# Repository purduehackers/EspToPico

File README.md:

# EspToPico
This is a converter board for an ESP32 to a Pi Pico for the purposes of the Sign Project.

The next revision of the board (3) should fix the following problems:
- It is impossible to program the board without resorting to using the bodged boot button. The official ESP32 dev board uses the serial chip to reset the ESP32 and put it in boot mode. Schematics are available online. This would be ideal.
- The button switch and LED lines had to be reversed here since the LED line was sent to an input-only pin. I reversed the labels for rev 2, but now there is a mismatch to the motherboard. This could be fixed later but it doesn't matter very much.
- The EEPROM MOSI, SCK, and CS lines are assigned to an input-only pin, rendering the EEPROM inaccessible. The ESP32 has enough storage to make this a non-issue, but it is still a problem. The easiest fix would be to switch the EEPROM MISO and MOSI lines then move the SCK and CS lines to regular GPIOs like GPIO 2 and 13.

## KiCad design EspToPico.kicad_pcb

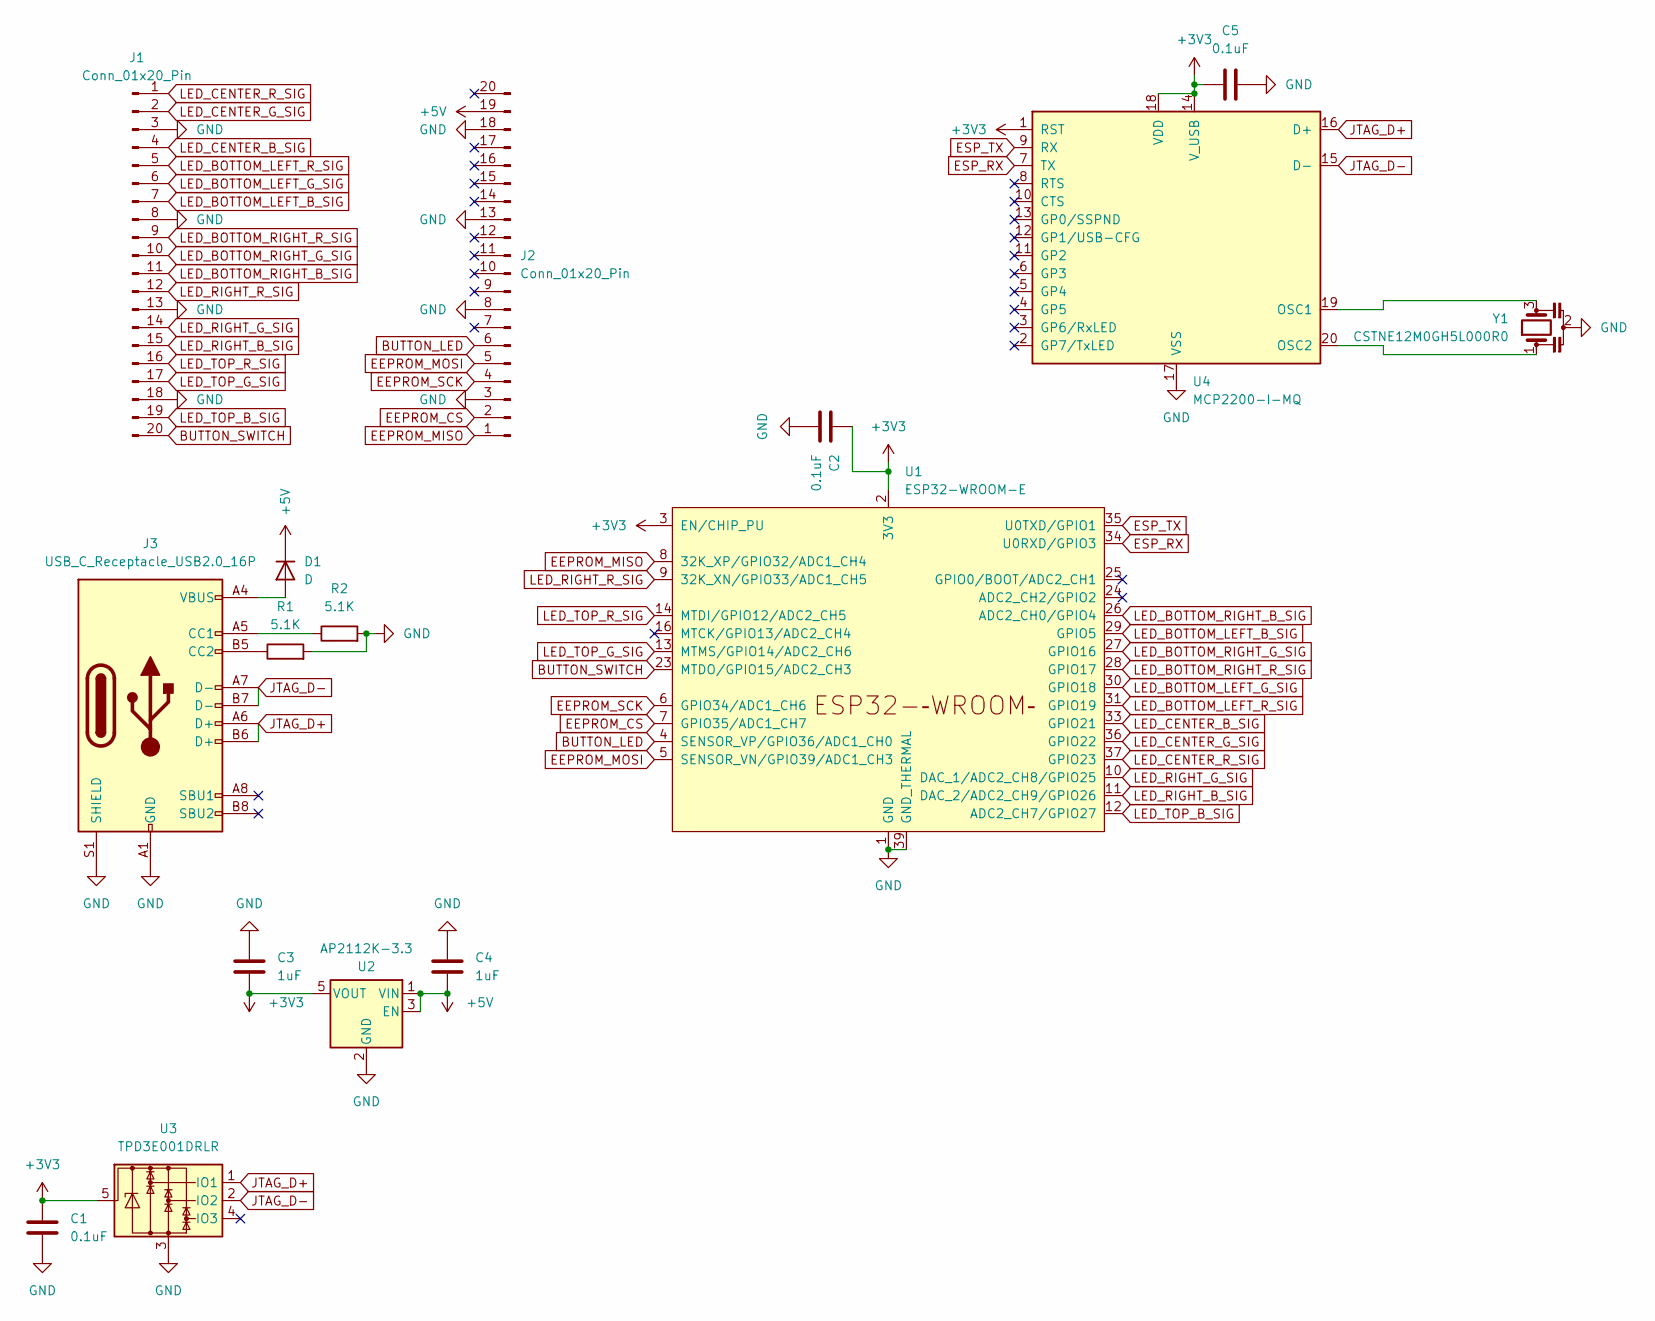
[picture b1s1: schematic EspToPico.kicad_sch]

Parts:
C1, C2: 0.1uF; C_0402_1005Metric
C3, C4: 1uF; C_0402_1005Metric
C5: 0.1uF
D1: D; D_SOD-323; LCSC C78740
J1, J2: Conn_01x20_Pin; PinHeader_1x20_P2.54mm_Vertical
J3: USB_C_Receptacle_USB2.0_16P; USB_C_Receptacle_GCT_USB4105-xx-A_16P_TopMnt_Horizontal; LCSC C2835315
R1, R2: 5.1K; R_0402_1005Metric
U1: ESP32-WROOM-E; ESP32-WROOM-32E
U2: AP2112K-3.3; SOT-23-5
U3: TPD3E001DRLR; SOT-553; LCSC C470828
U4: MCP2200-I-MQ; QFN-20-1EP_5x5mm_P0.65mm_EP3.35x3.35mm
Y1: CSTNE12M0GH5L000R0; CSTCE12M0G15L

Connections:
+3V3: C1.1, C2.1, C3.2, C5.1, U1.2 (3V3), U1.3 (EN/CHIP_PU), U2.5 (VOUT), U3.5, U4.1 (RST), U4.14 (V_USB), U4.18 (VDD)
+5V: C4.2, D1.1 (K), J2.19, U2.1 (VIN), U2.3 (EN)
BUTTON_LED: J2.6, U1.4 (SENSOR_VP/GPIO36/ADC1_CH0)
BUTTON_SWITCH: J1.20, U1.23 (MTDO/GPIO15/ADC2_CH3)
EEPROM_CS: J2.2, U1.7 (GPIO35/ADC1_CH7)
EEPROM_MISO: J2.1, U1.8 (32K_XP/GPIO32/ADC1_CH4)
EEPROM_MOSI: J2.5, U1.5 (SENSOR_VN/GPIO39/ADC1_CH3)
EEPROM_SCK: J2.4, U1.6 (GPIO34/ADC1_CH6)
ESP_RX: U1.34 (U0RXD/GPIO3), U4.7 (TX)
ESP_TX: U1.35 (U0TXD/GPIO1), U4.9 (RX)
GND: C1.2, C2.2, C3.1, C4.1, C5.2, J1.3, J1.8, J1.13, J1.18, J2.3, J2.8, J2.13, J2.18, J3.A1 (GND), J3.A12 (GND), J3.B1 (GND), J3.B12 (GND), J3.S1 (SHIELD), R1.2, R2.2, U1.1 (GND), U1.15 (GND), U1.38 (GND), U1.39 (GND_THERMAL), U2.2 (GND), U3.3, U4.17 (VSS), Y1.2
JTAG_D+: J3.A6 (D+), J3.B6 (D+), U3.1 (IO1), U4.16 (D+)
JTAG_D-: J3.A7 (D-), J3.B7 (D-), U3.2 (IO2), U4.15 (D-)
LED_BOTTOM_LEFT_B_SIG: J1.7, U1.29 (GPIO5)
LED_BOTTOM_LEFT_G_SIG: J1.6, U1.30 (GPIO18)
LED_BOTTOM_LEFT_R_SIG: J1.5, U1.31 (GPIO19)
LED_BOTTOM_RIGHT_B_SIG: J1.11, U1.26 (ADC2_CH0/GPIO4)
LED_BOTTOM_RIGHT_G_SIG: J1.10, U1.27 (GPIO16)
LED_BOTTOM_RIGHT_R_SIG: J1.9, U1.28 (GPIO17)
LED_CENTER_B_SIG: J1.4, U1.33 (GPIO21)
LED_CENTER_G_SIG: J1.2, U1.36 (GPIO22)
LED_CENTER_R_SIG: J1.1, U1.37 (GPIO23)
LED_RIGHT_B_SIG: J1.15, U1.11 (DAC_2/ADC2_CH9/GPIO26)
LED_RIGHT_G_SIG: J1.14, U1.10 (DAC_1/ADC2_CH8/GPIO25)
LED_RIGHT_R_SIG: J1.12, U1.9 (32K_XN/GPIO33/ADC1_CH5)
LED_TOP_B_SIG: J1.19, U1.12 (ADC2_CH7/GPIO27)
LED_TOP_G_SIG: J1.17, U1.13 (MTMS/GPIO14/ADC2_CH6)
LED_TOP_R_SIG: J1.16, U1.14 (MTDI/GPIO12/ADC2_CH5)
unnamed: D1.2 (A), J3.A4 (VBUS), J3.A9 (VBUS), J3.B4 (VBUS), J3.B9 (VBUS)
unnamed: J3.A5 (CC1), R2.1
unnamed: J3.B5 (CC2), R1.1
unnamed: U4.19 (OSC1), Y1.3
unnamed: U4.20 (OSC2), Y1.1

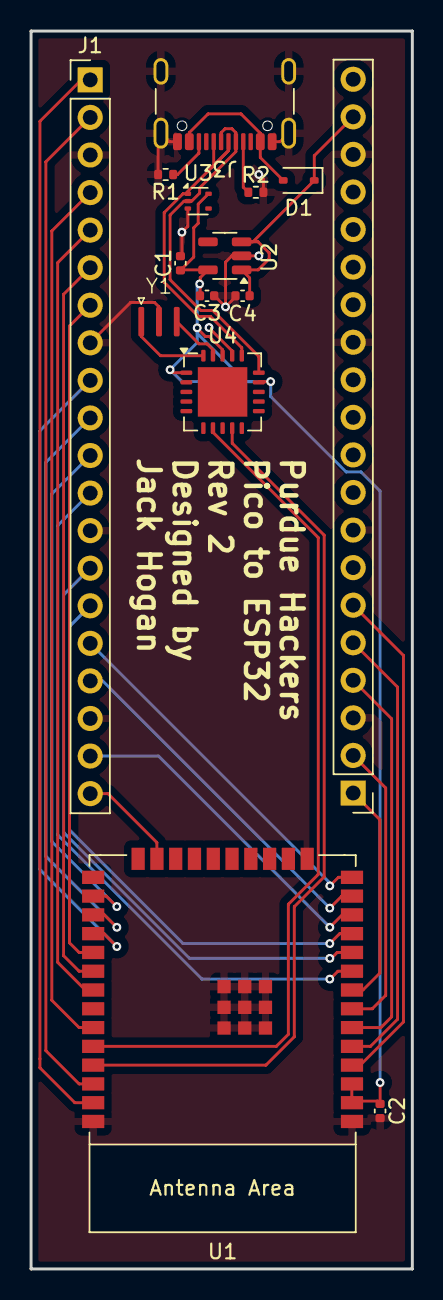
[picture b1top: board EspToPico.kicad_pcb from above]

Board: 2 copper layers, 25.8 x 83.7 mm, 15 parts (0 on the bottom side), 33 nets.

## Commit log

2024-08-24 Initial
2024-08-24 Removed sleep depravation
2024-08-25 Layout
2024-08-26 Added capacitors to the voltage regulator, added through-hole to the ESP32 for hand-soldering, and updated some routing.
2024-09-23 Started conversion to ESP32
2024-09-24 Updated to ESP32
2024-09-24 Fixed silkscreen
2024-09-24 Electrical and Routing fixes
2024-10-12 Reversed button switch and LED pins since the original LED pin is input only
2024-10-12 Added README
2024-10-12 Remove lock
2024-10-12 Added EEPROM fix suggestion
